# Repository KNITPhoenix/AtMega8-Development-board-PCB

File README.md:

# AtMega8-Development-board-PCB
This is the PCB design of AtMega8 development board on EagleCAD software with PORT D as input having PD0 to PD3 as input GPIO and PORT C as ouput having PC0 to PC3 as ouput GPIO. A L293D motor driver is connected with PC0 to PC3 to drive it.

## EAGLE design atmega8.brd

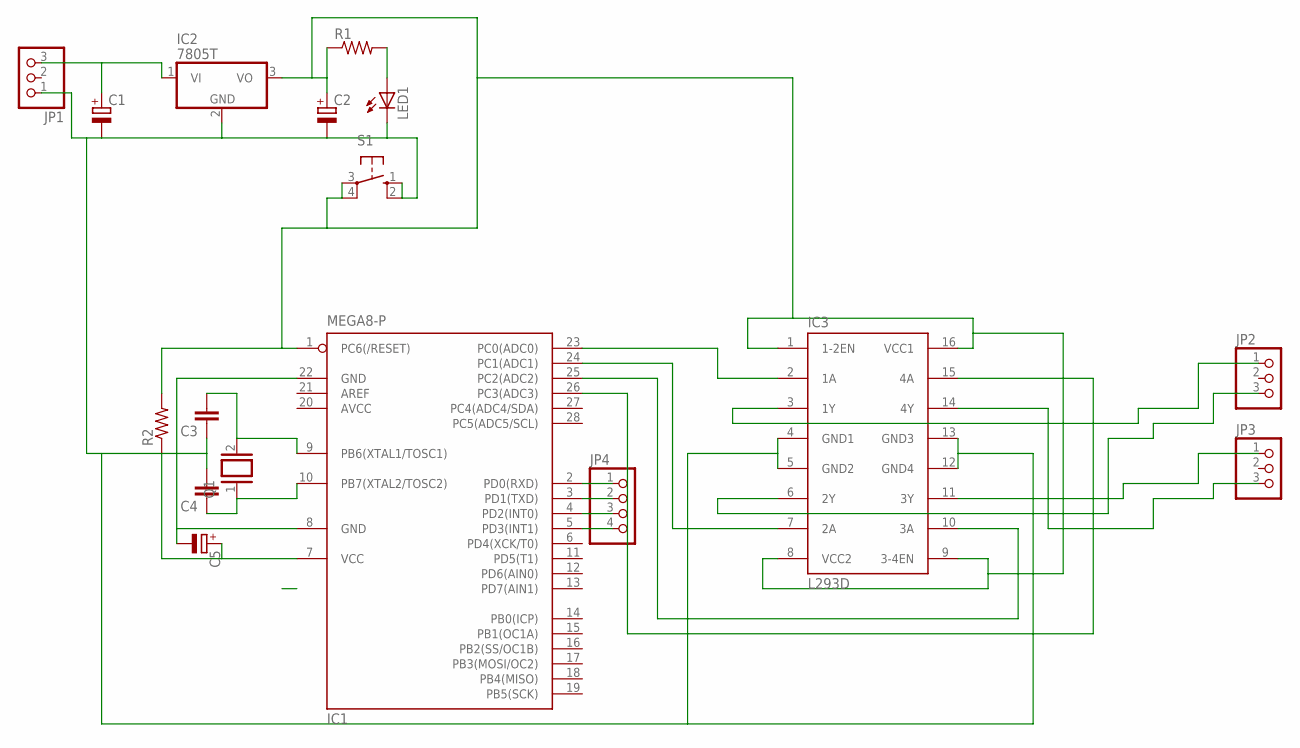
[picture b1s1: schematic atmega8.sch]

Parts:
C1, C2, C5: CPOL-EUE5-6; E5-6
C3, C4: C-EU025-025X050; C025-025X050
IC1: MEGA8-P; DIL28-3
IC2: 7805T; TO220H
IC3: L293D; DIL16
JP1, JP2, JP3: PINHD-1X3; 1X03
JP4: PINHD-1X4; 1X04
LED1: LED_ELD260; LED_LD260
Q1: XTAL/S; QS
R1, R2: R-US_0204/7; 0204/7
S1: 10-XX; B3F-10XX

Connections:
AVCC: IC1.20 (AVCC)
unnamed: C1.+, IC2.1 (VI), JP1.3
unnamed: C1.-, C2.-, C3.1, C4.2, C5.-, IC1.8 (GND), IC1.22 (GND), IC2.2 (GND), IC3.4 (GND1), IC3.5 (GND2), IC3.12 (GND4), IC3.13 (GND3), JP1.1, LED1.K (C), S1.1 (S), S1.2 (S1)
unnamed: C5.+, IC1.7 (VCC), R2.1
unnamed: LED1.A, R1.2
unnamed: C4.1, IC1.10 (PB7(XTAL2/TOSC2)), Q1.1
unnamed: IC1.23 (PC0(ADC0)), IC3.2 (1A)
unnamed: IC1.24 (PC1(ADC1)), IC3.7 (2A)
unnamed: C3.2, IC1.9 (PB6(XTAL1/TOSC1)), Q1.2
unnamed: C2.+, IC1.1 (PC6(/RESET)), IC2.3 (VO), IC3.1 (1-2EN), IC3.8 (VCC2), IC3.9 (3-4EN), IC3.16 (VCC1), R1.1, R2.2, S1.3, S1.4 (P1)
unnamed: IC1.25 (PC2(ADC2)), IC3.10 (3A)
unnamed: IC1.26 (PC3(ADC3)), IC3.15 (4A)
unnamed: IC3.3 (1Y), JP2.1
unnamed: IC3.6 (2Y), JP2.3
unnamed: IC3.11 (3Y), JP3.1
unnamed: IC3.14 (4Y), JP3.3
unnamed: IC1.2 (PD0(RXD)), JP4.1
unnamed: IC1.3 (PD1(TXD)), JP4.2
unnamed: IC1.4 (PD2(INT0)), JP4.3
unnamed: IC1.5 (PD3(INT1)), JP4.4

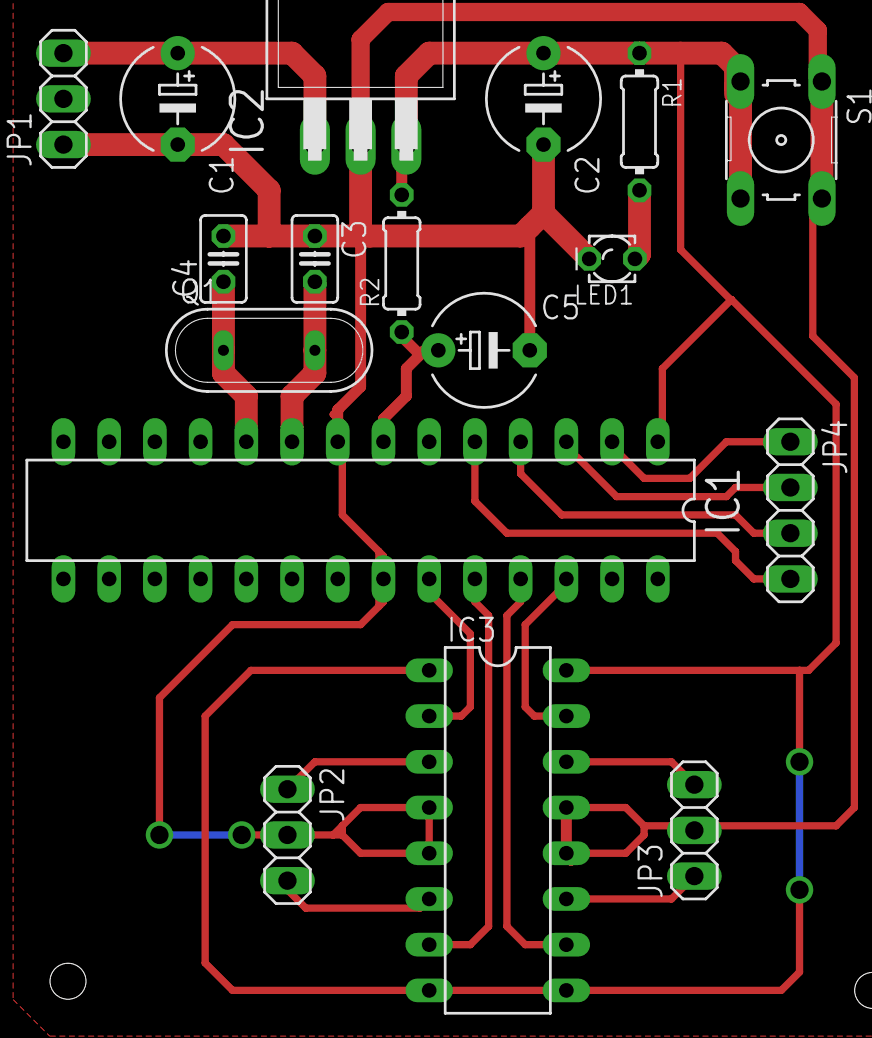
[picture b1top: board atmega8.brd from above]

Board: 2 copper layers, 17 parts (0 on the bottom side), 19 nets.

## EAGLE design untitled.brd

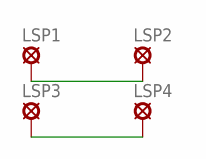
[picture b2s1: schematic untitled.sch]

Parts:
LSP1, LSP2, LSP3, LSP4: SE13

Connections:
unnamed: LSP1.MP, LSP2.MP
unnamed: LSP3.MP, LSP4.MP

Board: 2 copper layers, 4 parts (0 on the bottom side), 2 nets, no tracks yet.
